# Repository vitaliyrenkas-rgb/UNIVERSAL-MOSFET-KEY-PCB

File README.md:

# Слава Україні, козацтво!
# UNIVERSAL MOSFET KEY PCB — REV-A

# DISCLAIMER: Oct-11th, 2026. Manifacture confirmed. Actual device is working as expected. \ 11 Жовтня 2026. ФІЗИЧНА ПРИДАТНІСТЬ ПІДТВЕРДЖЕНА!

# Key Feature from my POV: PCB dimensions are 30x30mm, which makes it suitable for smail DIY embedded devices\IoT
# Ключова для мене фіча, що приймалась за основу при розробці - малі габарити 30х30мм, що робить її зручною для використання в маленьких embedded-самодєлках.

Compact configurable MOSFET carrier board for small power-switching and control applications.

REV-A combines two configurable MOSFET stages on one PCB:

- U1 — N-channel MOSFET
- U2 — P-channel MOSFET

The stages may be used independently or linked together using solder jumpers.

Typical applications:

- touch-controlled power switch;
- high-side power switching;
- TP4056 input power control;
- standalone low-side N-MOSFET switching;
- status / power indication;
- small embedded power-control circuits.

The board uses commonly available SOT-23 MOSFETs, 1206 passive components and optional JST-PH 2.0 mm connectors.

---

## Hardware

### MOSFETs

U1 — N-MOSFET:
- AO3400A
- IRLML6344
- or another electrically compatible SOT-23 N-channel MOSFET

U2 — P-MOSFET:
- AO3401A
- or another electrically compatible SOT-23 P-channel MOSFET

For the devices used in this project:

1 = Gate  
2 = Source  
3 = Drain

### Passive components

- R1–R5 — 1206
- D1 — LED 1206
- JP1–JP4 — normally-open solder jumpers

### Connectors

The PCB provides optional JST-PH 2.0 mm footprints.

POWER:

| Pin | Signal |
| --- | --- |
| 1 | VCC |
| 2 | GND |

N-MOS:

| Pin | Signal |
| --- | --- |
| 1 | N-CTRL |
| 2 | N-IN |
| 3 | N-OUT |

P-MOS:

| Pin | Signal |
| --- | --- |
| 1 | P-CTRL |
| 2 | P-IN |
| 3 | P-OUT |

The JST connectors are optional. They may be left unpopulated and the pads may be used for direct wiring.

---

## Circuit structure

### N-MOS stage

N-CTRL → R1 → Gate U1

R2 connects Gate U1 to Source U1.

Source U1 = N-IN  
Drain U1 = N-OUT

Therefore:

N-CTRL → R1 → N-GATE  
N-GATE → Gate U1  
N-GATE → R2 → N-IN  
N-IN → Source U1  
N-OUT → Drain U1

### P-MOS stage

P-CTRL → R3 → Gate U2

R4 connects Gate U2 to Source U2.

Source U2 = P-IN  
Drain U2 = P-OUT

Therefore:

P-CTRL → R3 → P-GATE  
P-GATE → Gate U2  
P-GATE → R4 → P-IN  
P-IN → Source U2  
P-OUT → Drain U2

### Status LED

P-OUT → R5 → D1 → JP4 → GND

D1 polarity:

Anode = +  
Cathode = -

The onboard LED is intended as a status / power indicator, not as a high-power lighting output.

---

# Solder jumper configuration

All four jumpers are normally OPEN.

## JP1 — N-IN to GND

JP1 connects:

N-IN ↔ GND

Close JP1 when U1 is used as a conventional low-side N-MOSFET switch referenced to board ground.

JP1 CLOSED:

N-IN = GND

Typical low-side connection:

Load positive → power supply positive  
Load negative → N-OUT  
U1 Source → N-IN → JP1 → GND  
Control signal → N-CTRL

JP1 OPEN:

N-IN remains electrically independent and may be connected externally.

---

## JP2 — P-IN to VCC

JP2 connects:

P-IN ↔ VCC

Close JP2 when U2 is used as a conventional high-side P-MOSFET referenced to board VCC.

JP2 CLOSED:

P-IN = VCC

JP2 OPEN:

P-IN remains electrically independent and may be connected externally.

---

## JP3 — N-OUT to P-CTRL

JP3 connects:

N-OUT ↔ P-CTRL

This links both MOSFET stages into a cascaded N-MOS → P-MOS high-side switch.

With JP1, JP2 and JP3 closed:

N-CTRL HIGH  
→ U1 turns ON  
→ N-OUT pulls P-CTRL LOW  
→ U2 Gate is pulled below its Source  
→ U2 turns ON  
→ P-OUT becomes powered

N-CTRL LOW  
→ U1 turns OFF  
→ R4 pulls U2 Gate back toward P-IN / Source  
→ U2 turns OFF

This configuration provides an active-HIGH control input for a P-channel high-side switch.

JP3 OPEN:

The N-MOS and P-MOS stages remain independent.

---

## JP4 — LED to GND

JP4 connects the cathode side of the onboard LED circuit to GND.

LED path:

P-OUT → R5 → D1 → JP4 → GND

JP4 CLOSED:

The onboard status LED is enabled.

JP4 OPEN:

The onboard LED circuit is disconnected from GND.

If the LED is not required, JP4 may simply remain open. R5 and/or D1 may also be left unpopulated depending on the application.

---

# Typical configurations

## Cascaded active-HIGH high-side switch

Typical configuration:

JP1 — CLOSED  
JP2 — CLOSED  
JP3 — CLOSED  
JP4 — optional

Connections:

VCC → supply positive  
GND → supply ground  
N-CTRL → control signal  
P-OUT → switched positive output

The N-MOSFET converts the active-HIGH input signal into the low Gate level required to turn the P-MOSFET on.

---

## Touch-controlled camera power switch

The topology was previously bench-tested successfully with a TTP223B touch sensor and the target camera power circuit.

Configuration:

U1 — IRLML6344  
U2 — AO3401A  
R1 — 1 kΩ  
R2 — 100 kΩ  
R3 — 0 Ω  
R4 — 10 kΩ  
R5 — DNP if the onboard LED is not required  
JP1 — CLOSED  
JP2 — CLOSED  
JP3 — CLOSED  
JP4 — optional

Connections:

VCC → BAT+  
GND → BAT−  
N-CTRL → TTP223B OUT  
P-OUT → switched positive output / camera switch circuit

For the tested red TTP223B module:

B jumper — CLOSED  
A jumper — OPEN  
Mode — toggle  
Output — active HIGH  
Startup state — OFF

Important: in the tested camera, the original functional donor slide switch still had to remain part of the circuit. Simply connecting the previously assumed switch pads was not sufficient for normal camera operation.

---

## RT-004 / TP4056 input power control
[RENTECH-004. DIY CAPACITY TESTER v.1.13. (v2.0 IN ACTIVE TESTING)](https://github.com/vitaliyrenkas-rgb/ESP32-Li-ion-Battery-Capacity-Tester-DIY)
Intended configuration:

U1 — AO3400A  
U2 — AO3401A  
R1 — 0 Ω  
R2 — 10 kΩ  
R3 — 0 Ω  
R4 — 10 kΩ  
JP1 — CLOSED  
JP2 — CLOSED  
JP3 — CLOSED  
JP4 — optional

Connections:

VCC → USB +5 V  
GND → common USB / ESP32 / TP4056 IN− ground  
N-CTRL → MCU GPIO  
P-OUT → TP4056 / HW-373 IN+

Logic:

GPIO HIGH → charger module receives input power  
GPIO LOW → charger module input power is disconnected

This configuration switches the positive input supply of the charger module.

The battery path and relay wiring are not switched or modified by this board.

Full REV-A integration of this configuration still requires bench validation.

---

## Standalone N-MOSFET switch

Configuration:

JP1 — CLOSED  
JP2 — OPEN  
JP3 — OPEN

U2 and its associated components may be left unpopulated if they are not required.

Connections:

N-CTRL → control signal / PWM  
N-OUT → load negative  
N-IN → GND through JP1  
Load positive → supply positive

---

## Standalone P-MOSFET switch

Configuration depends on the required control method.

For a conventional high-side P-MOSFET referenced to VCC:

JP2 — CLOSED  
JP3 — OPEN

P-IN is then tied to VCC.

External control may be applied through P-CTRL.

The control signal must respect the P-MOSFET Gate-to-Source voltage limits and must be appropriate for the supply voltage used.

---

# Important notes

- `0 Ω` means a physical zero-ohm resistor is installed.
- `DNP` means Do Not Populate.
- Leaving R1 unpopulated disconnects the external N-CTRL path from U1 Gate.
- Leaving R3 unpopulated disconnects the external P-CTRL path from U2 Gate.
- R2 always references U1 Gate to U1 Source.
- R4 always references U2 Gate to U2 Source.
- U1 Source and U2 Source are not permanently connected together.
- JP1 connects N-IN to GND only when closed.
- JP2 connects P-IN to VCC only when closed.
- JP3 links N-OUT to P-CTRL only when closed.
- JP4 enables the onboard LED return path to GND only when closed.
- A single P-channel MOSFET does not provide complete reverse-current isolation.
- Maximum current and thermal limits depend on the installed MOSFET, copper thickness, PCB conditions and actual application.
- REV-A is intended for small embedded electronics and is not characterized as a multi-ampere power switch.
- PWM capability depends on the installed MOSFET, Gate resistor values, drive source and load.

---

# REV-A status

- schematic complete;
- PCB routed;
- electrical DRC clean;
- 0 unconnected pads;
- 0 footprint errors;
- JST-PH 2.0 mm connector footprints;
- SOT-23 MOSFET footprints;
- 1206 resistors and LED;
- four configurable solder jumpers;
- onboard status LED;
- fabrication outputs prepared.

Remaining DRC warnings are related only to silkscreen graphics extending beyond the board edge around deliberately edge-mounted JST connectors. The connectors are intentionally positioned this way for easier insertion/removal and to preserve PCB space for components and labeling.

---

# Українська

# UNIVERSAL MOSFET KEY PCB — REV-A

Компактна конфігурована MOSFET-плата для керування живленням та інших невеликих комутаційних задач.

REV-A містить два MOSFET-каскади:

- U1 — N-канальний MOSFET
- U2 — P-канальний MOSFET

Каскади можна використовувати незалежно або об'єднати між собою паяними перемичками.

Типові застосування:

- сенсорний ключ живлення;
- high-side комутація живлення;
- керування вхідним живленням TP4056;
- окремий low-side N-MOSFET ключ;
- індикація стану / живлення;
- компактні вбудовані схеми керування живленням.

Плата використовує поширені MOSFET у корпусі SOT-23, пасивні компоненти 1206 та опційні JST-PH 2.0 мм.

---

## Компоненти

### MOSFET

U1 — N-MOSFET:

- AO3400A
- IRLML6344
- або інший електрично сумісний N-MOSFET у SOT-23 корпусі

U2 — P-MOSFET:

- AO3401A
- або інший електрично сумісний P-MOSFET у SOT-23 корпусі

Для MOSFET, використаних у цьому проєкті:

1 = Gate  
2 = Source  
3 = Drain

### Пасивні компоненти

- R1–R5 — 1206
- D1 — LED 1206
- JP1–JP4 — паяні перемички, початково OPEN

### Конектори

Передбачені посадкові місця під JST-PH 2.0 мм конектори.

POWER:

| Pin | Сигнал |
| --- | --- |
| 1 | VCC |
| 2 | GND |

N-MOS:

| Pin | Сигнал |
| --- | --- |
| 1 | N-CTRL |
| 2 | N-IN |
| 3 | N-OUT |

P-MOS:

| Pin | Сигнал |
| --- | --- |
| 1 | P-CTRL |
| 2 | P-IN |
| 3 | P-OUT |

JST-конектори не є обов'язковими. Їх можна не встановлювати й використовувати площадки для прямого підпаювання проводів.

---

## Структура схеми

### N-MOS каскад

N-CTRL → R1 → Gate U1

R2 з'єднує Gate U1 з Source U1.

Source U1 = N-IN  
Drain U1 = N-OUT

Тобто:

N-CTRL → R1 → N-GATE  
N-GATE → Gate U1  
N-GATE → R2 → N-IN  
N-IN → Source U1  
N-OUT → Drain U1

### P-MOS каскад

P-CTRL → R3 → Gate U2

R4 з'єднує Gate U2 з Source U2.

Source U2 = P-IN  
Drain U2 = P-OUT

Тобто:

P-CTRL → R3 → P-GATE  
P-GATE → Gate U2  
P-GATE → R4 → P-IN  
P-IN → Source U2  
P-OUT → Drain U2

### LED-індикація

P-OUT → R5 → D1 → JP4 → GND

Полярність D1:

Анод = +  
Катод = -

LED призначений для індикації стану / живлення, а не як силовий вихід для підсвітки.

---

# Конфігурація перемичок

Усі чотири джампери за замовчуванням OPEN.

## JP1 — N-IN → GND

JP1 з'єднує:

N-IN ↔ GND

JP1 потрібно замкнути, якщо U1 використовується як звичайний low-side N-MOSFET ключ із прив'язкою до загальної землі плати.

JP1 CLOSED:

N-IN = GND

Типове підключення:

плюс навантаження → плюс живлення  
мінус навантаження → N-OUT  
Source U1 → N-IN → JP1 → GND  
керування → N-CTRL

JP1 OPEN:

N-IN залишається незалежним зовнішнім контактом.

---

## JP2 — P-IN → VCC

JP2 з'єднує:

P-IN ↔ VCC

JP2 потрібно замкнути, якщо U2 використовується як типовий high-side P-MOSFET ключ із прив'язкою Source до VCC.

JP2 CLOSED:

P-IN = VCC

JP2 OPEN:

P-IN залишається незалежним зовнішнім контактом.

---

## JP3 — N-OUT → P-CTRL

JP3 з'єднує:

N-OUT ↔ P-CTRL

Ця перемичка об'єднує N-MOS та P-MOS у каскадний high-side ключ.

При замкнених JP1, JP2 та JP3:

N-CTRL HIGH  
→ U1 відкривається  
→ N-OUT тягне P-CTRL вниз  
→ Gate U2 стає нижчим за Source  
→ U2 відкривається  
→ P-OUT отримує живлення

N-CTRL LOW  
→ U1 закривається  
→ R4 підтягує Gate U2 назад до P-IN / Source  
→ U2 закривається

Таким чином отримуємо high-side P-MOSFET ключ з активним HIGH керуючим входом.

JP3 OPEN:

N-MOS та P-MOS каскади працюють незалежно.

---

## JP4 — LED → GND

JP4 підключає катодний бік LED-вузла до GND.

Шлях LED:

P-OUT → R5 → D1 → JP4 → GND

JP4 CLOSED:

Вбудована LED-індикація активна.

JP4 OPEN:

LED-вузол від'єднаний від GND.

Якщо індикація не потрібна, JP4 можна просто залишити розімкненою. За потреби R5 та/або D1 також можна не встановлювати.

---

# Типові конфігурації

## Каскадний active-HIGH high-side ключ

Типова конфігурація:

JP1 — CLOSED  
JP2 — CLOSED  
JP3 — CLOSED  
JP4 — за потреби

Підключення:

VCC → плюс живлення  
GND → земля  
N-CTRL → керуючий сигнал  
P-OUT → комутований плюс

N-MOSFET перетворює активний HIGH керуючий сигнал у LOW на Gate P-MOSFET, необхідний для його відкривання.

---

## Сенсорний ключ живлення камери\низьковольтового пристрою (3.3-5В)

Ця топологія була успішно перевірена на попередній макетній збірці з TTP223B та конкретною камерою.

Конфігурація:

U1 — IRLML6344  
U2 — AO3401A  
R1 — 1 kΩ  
R2 — 100 kΩ  
R3 — 0 Ω  
R4 — 10 kΩ  
R5 — DNP, якщо LED на платі не потрібен  
JP1 — CLOSED  
JP2 — CLOSED  
JP3 — CLOSED  
JP4 — за потреби

Підключення:

VCC → BAT+  
GND → BAT−  
N-CTRL → OUT TTP223B  
P-OUT → комутований плюс / ланцюг штатного перемикача камери

Для перевіреної червоної плати TTP223B:

B — CLOSED  
A — OPEN  
режим — toggle  
активний рівень — HIGH  
стартовий стан — OFF

Важливо: у конкретній протестованій камері в схемі також мав залишатися справний донорський штатний повзунковий перемикач. Простого з'єднання раніше визначених контактних площадок виявилося недостатньо для нормальної роботи камери.

---

## RT-004 / керування входом TP4056
[RENTECH RT-004 DIY CAPACITY TESTER V1.13 (КЛЮЧ ВИКОРИСТАНИЙ У V2.0, ЩО НАРАЗІ АКТИВНО ТЕСТУЄТЬСЯ](https://github.com/vitaliyrenkas-rgb/ESP32-Li-ion-Battery-Capacity-Tester-DIY)
Запланована конфігурація:

U1 — AO3400A  
U2 — AO3401A  
R1 — 0 Ω  
R2 — 10 kΩ  
R3 — 0 Ω  
R4 — 10 kΩ  
JP1 — CLOSED  
JP2 — CLOSED  
JP3 — CLOSED  
JP4 — за потреби

Підключення:

VCC → USB +5 V  
GND → спільна земля USB / ESP32 / TP4056 IN−  
N-CTRL → GPIO мікроконтролера  
P-OUT → TP4056 / HW-373 IN+

Логіка:

GPIO HIGH → зарядний модуль отримує живлення  
GPIO LOW → живлення входу зарядного модуля вимкнене

Ця конфігурація комутує саме вхідний плюс зарядного модуля.

Батарейний тракт та підключення реле ця плата не змінює.

Повний bench PASS інтеграції REV-A у RT-004 поки не підтверджений.

---

## Окремий N-MOSFET ключ

Конфігурація:

JP1 — CLOSED  
JP2 — OPEN  
JP3 — OPEN

U2 та його обв'язку можна не встановлювати, якщо вони не потрібні.

Підключення:

N-CTRL → керування / PWM  
N-OUT → мінус навантаження  
N-IN → GND через JP1  
плюс навантаження → плюс його живлення

---

## Окремий P-MOSFET ключ

Конфігурація залежить від конкретного способу керування.

Для типового high-side P-MOSFET із Source на VCC:

JP2 — CLOSED  
JP3 — OPEN

У такому випадку P-IN під'єднаний до VCC.

Зовнішнє керування подається через P-CTRL.

Керуючий сигнал повинен відповідати допустимому Gate-to-Source voltage встановленого P-MOSFET та напрузі живлення конкретного виробу.

---

# Важливі примітки

- `0 Ω` означає фізично встановлений нульовий резистор.
- `DNP` означає Do Not Populate — компонент не встановлювати.
- Якщо R1 не встановлений, зовнішній N-CTRL від'єднаний від Gate U1.
- Якщо R3 не встановлений, зовнішній P-CTRL від'єднаний від Gate U2.
- R2 завжди підтягує Gate U1 до його власного Source.
- R4 завжди підтягує Gate U2 до його власного Source.
- Source U1 та Source U2 напряму між собою не з'єднані.
- JP1 з'єднує N-IN із GND тільки після замикання.
- JP2 з'єднує P-IN із VCC тільки після замикання.
- JP3 з'єднує N-OUT із P-CTRL тільки після замикання.
- JP4 підключає LED-вузол до GND тільки після замикання.
- Один P-MOSFET не забезпечує повної ізоляції від зворотного струму.
- Максимальний струм і нагрів залежать від конкретного MOSFET, товщини міді, умов охолодження та конкретного застосування.
- REV-A призначена для невеликих embedded-пристроїв і не характеризувалась як багатoамперний силовий модуль.
- Допустимий PWM залежить від встановленого MOSFET, номіналів Gate-резисторів, джерела керування та навантаження.

---

# Статус REV-A

- схема завершена;
- PCB протрасована;
- електричний DRC чистий;
- 0 unconnected pads;
- 0 footprint errors;
- посадкові JST-PH 2.0 мм;
- MOSFET SOT-23;
- резистори та LED 1206;
- чотири конфігураційні solder jumpers;
- вбудована LED-індикація;
- fabrication outputs підготовлені.

Залишкові DRC warnings стосуються тільки елементів шовкографії JST-конекторів, що виходять за Edge.Cuts. JST навмисно винесені до країв плати для зручного підключення та від'єднання конекторів, а також для економії внутрішнього простору PCB.

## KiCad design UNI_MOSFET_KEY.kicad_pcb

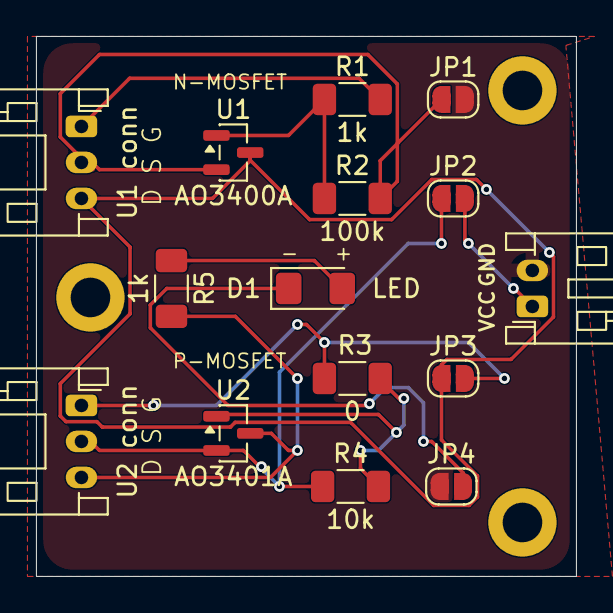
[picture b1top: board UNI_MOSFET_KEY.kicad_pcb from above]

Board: 2 copper layers, 30.0 x 30.0 mm, 15 parts (0 on the bottom side), 12 nets.

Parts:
D1: LED; D_1206_3216Metric_Pad1.42x1.75mm_HandSolder
J1: Conn_01x02; JST_PH_S2B-PH-K_1x02_P2.00mm_Horizontal
JP1, JP2, JP3, JP4: SolderJumper_2_Open; SolderJumper-2_P1.3mm_Open_RoundedPad1.0x1.5mm
R1, R5: 1k; R_1206_3216Metric_Pad1.30x1.75mm_HandSolder
R2: 100k; R_1206_3216Metric_Pad1.30x1.75mm_HandSolder
R3: 0; R_1206_3216Metric_Pad1.30x1.75mm_HandSolder
R4: 10k; R_1206_3216Metric_Pad1.30x1.75mm_HandSolder
U1: AO3400A; SOT-23
U1 conn, U2 conn: Conn_01x03; JST_PH_S3B-PH-K_1x03_P2.00mm_Horizontal
U2: AO3401A; SOT-23

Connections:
/GND: J1.2, JP1.2 (B), JP4.1 (A)
/N-CTRL: R1.2, U1 conn.1
/N-IN(S): JP1.1 (A), R2.2, U1.2 (S), U1 conn.2
/N-OUT(D): JP3.1 (A), U1.3 (D), U1 conn.3
/P-CTRL: JP3.2 (B), R3.1, U2 conn.1
/P-IN(S): JP2.1 (A), R4.1, U2.2 (S), U2 conn.2
/P-OUT(D): R5.2, U2.3 (D), U2 conn.3
/VCC: J1.1, JP2.2 (B)
unnamed: D1.2 (A), R5.1
unnamed: D1.1 (K), JP4.2 (B)
unnamed: R1.1, R2.1, U1.1 (G)
unnamed: R3.2, R4.2, U2.1 (G)
